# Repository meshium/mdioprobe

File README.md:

# mdioprobe v2

An MDIO probe on a custom STM32G474CET6 board: it watches a Clause-22 bus
without touching it, and it can drive one.

- **Passive capture.** The analogue MDIO and MDC lines go through comparators
  with a DAC threshold; TIM3 counts 32 MDC edges from the start bit, an HRTIM
  latch turns that into chip-select for SPI2 in slave mode, and the CPU only
  decodes finished frames. No per-frame software setup, so a busy bus does
  not outrun it — 284350 consecutive frames from an 88E6321 PPU at 6.25 MHz
  MDC with no decode errors, ring overruns or DMA faults.
- **Active master.** Bit-banged Clause 22 up to 2.5 MHz through a tri-state
  buffer powered from a programmable supply, so MDC comes out at the target's
  own logic level. Reads go back through the same comparator front end, which
  is why no receive-side translator is needed.
- **Level-agnostic.** The target's rail is measured, not assumed: 1.8, 2.5 and
  3.3 V buses are detected and every threshold derives from that one number.
  Until a rail is known, capture and the master both refuse to run.
- **Chip identification.** Registers 2 and 3 are looked up in a table
  extracted from the Linux kernel sources — 302 PHYs and 120 DSA switches,
  frozen into the firmware, so it works on a blank volume.

The command interface is a MicroPython CLI over USB CDC ACM, with history,
TAB completion, output redirection to files and a QSPI NOR volume for scripts
and logs.

```
mdio /flash> probe
phy 05: 4f51e91a  YT8531S Gigabit Ethernet
1 device(s) answered with an identifier

mdio /flash> read 5 2-3
reg 0x02 = 0x4f51
reg 0x03 = 0xe91a
```

## Building

Zephyr, with the board definition in-tree. The MicroPython submodule is
needed first:

```
git submodule update --init --recursive
./build.sh              # build
./build.sh flash        # build and flash over SWD
```

`build.sh` is the only supported entry point. It sources the Zephyr
environment, pins a toolchain and calls `west`, and it takes nothing on trust
from the machine it runs on:

| | |
| :-- | :-- |
| `ZEPHYR_BASE` | the Zephyr tree; defaults to `~/zephyrproject/zephyr` |
| `MDIOPROBE_SDK` | which SDK; defaults to the newest `~/zephyr-sdk-*` |
| `MDIOPROBE_VENV` | virtualenv to activate, and only when `west` is not already on `PATH` |

If your Zephyr environment is already active, the script uses it and changes
nothing. If a path is missing it says which one, rather than failing deep
inside CMake.

## Console

There is no VCP on the board. The log and the CLI share **USB CDC ACM**
(`/dev/tty.usbmodem*`); SWD on PA13/PA14/PB3 is for debugging. `tools/con.py`
is the bench driver for the console.

`help` lists the commands and `help <command>` explains one. USB is either the
console or a mass-storage device, never both at once: `msd` hands the volume
to the host and takes the console away until the probe is unplugged.

## Layout

```
src/            firmware; the public surface is include/mdioprobe_api.h alone
src/python/     the CLI, frozen into the image
boards/         the board definition (HWMv2)
hardware/       KiCad project: schematic, PCB, gerbers
docs/CAPTURE.md   how a frame is captured, end to end
docs/HARDWARE.md  pinout, connector, and what the schematic actually does
tools/con.py    console driver for the bench
tools/upload.py put files on the volume without unplugging
```

Zephyr APIs are used for ADC, GPIO, flash, UART, I2C and USB; the comparators,
TIM3, HRTIM, the SPI2 slave ring and the bit-bang master are driven through
STM32Cube LL and direct register writes, because Zephyr does not expose the
COMP-to-timer crossbars and its STM32 SPI slave driver races its own DMA.

## Status

Pre-release. Bring-up is complete and verified on hardware, including capture
against a real external master. Not yet exercised: the `uart` and `i2c`
connector personalities, and the short-circuit latch on the programmable
supply.

## Licence

Two objects, licensed separately, which is the usual practice for open
hardware and the only one that reads sensibly — a software licence does not
define what "object form" or "linking" mean for a printed circuit board.

- **Firmware and everything else: Apache-2.0**, text in `LICENSE`. The image
  is a static link, so a binary release carries Zephyr, MicroPython, the
  STM32Cube LL drivers, FatFs and picolibc with it; `NOTICE` lists each
  component and its terms and belongs with the binary, not only with the
  source.
- **The board, under `hardware/`: CERN-OHL-P-2.0**, text in
  `hardware/LICENSE`. Permissive, to match the firmware, and written for
  hardware — unlike a Creative Commons licence it grants patent rights, which
  for a circuit board is the part that matters.

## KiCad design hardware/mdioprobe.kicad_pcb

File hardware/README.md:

# mdioprobe v2 — board

SPDX-License-Identifier: CERN-OHL-P-2.0

KiCad 8 project for the probe: schematic, PCB, the footprints that are not in
the standard libraries, and a gerber set.

```
mdioprobe.kicad_sch     schematic
mdioprobe.kicad_pcb     board
mdioprobe.netlist       netlist
footprints.pretty/      footprints not in the KiCad libraries
gbr/                    gerbers and drill files
```

The KiCad footprint cache (`fp-info-cache`) and per-user project settings
(`*.kicad_prl`) are not tracked: KiCad rebuilds the first from the libraries
on demand, and the second is local to whoever opened the project.

## Licence

Everything in this directory is under the **CERN Open Hardware Licence
Version 2 — Permissive** (`LICENSE` here, SPDX `CERN-OHL-P-2.0`).

**The firmware is not.** The rest of the repository is Apache-2.0, with its
own `LICENSE` and `NOTICE` at the top level. Hardware and software are
different objects in law and are licensed separately, which is the usual
practice and the only one that makes sense: a software licence has nothing to
say about what "object form" or "linking" mean for a printed circuit board.

CERN-OHL-P rather than a Creative Commons licence, for two reasons. It is
written for hardware — it defines Source as the design files, Product as the
thing you build from them, and it covers making and having made, none of
which a licence written for creative works addresses. And it grants patent
rights (§6.1), which CC 4.0 explicitly does not (§2(b)(2): "Patent and
trademark rights are not licensed"). For hardware that gap is in exactly the
place the risk lives — the design files would be yours to copy while the
right to build the thing was not.

Permissive rather than the reciprocal variant (CERN-OHL-S): it matches the
firmware's Apache-2.0, and the point of publishing this board is that people
can use it, including inside something they do not open.

There is no warranty and no liability, per sections 5 and 8 of the licence.
This is a bench instrument, not a certified one.

## What it is

STM32G474CET6 in LQFP48. Comparators with a DAC threshold on the MDIO and MDC
inputs, a tri-state buffer on the MDC output powered from a programmable
soft-LDO so the probe drives at the target's own logic level, QSPI NOR for
storage, and USB.

`docs/HARDWARE.md` in the repository root is the pinout, the connector, and
the parts of the schematic worth knowing about before changing anything —
including what the next board revision needs.

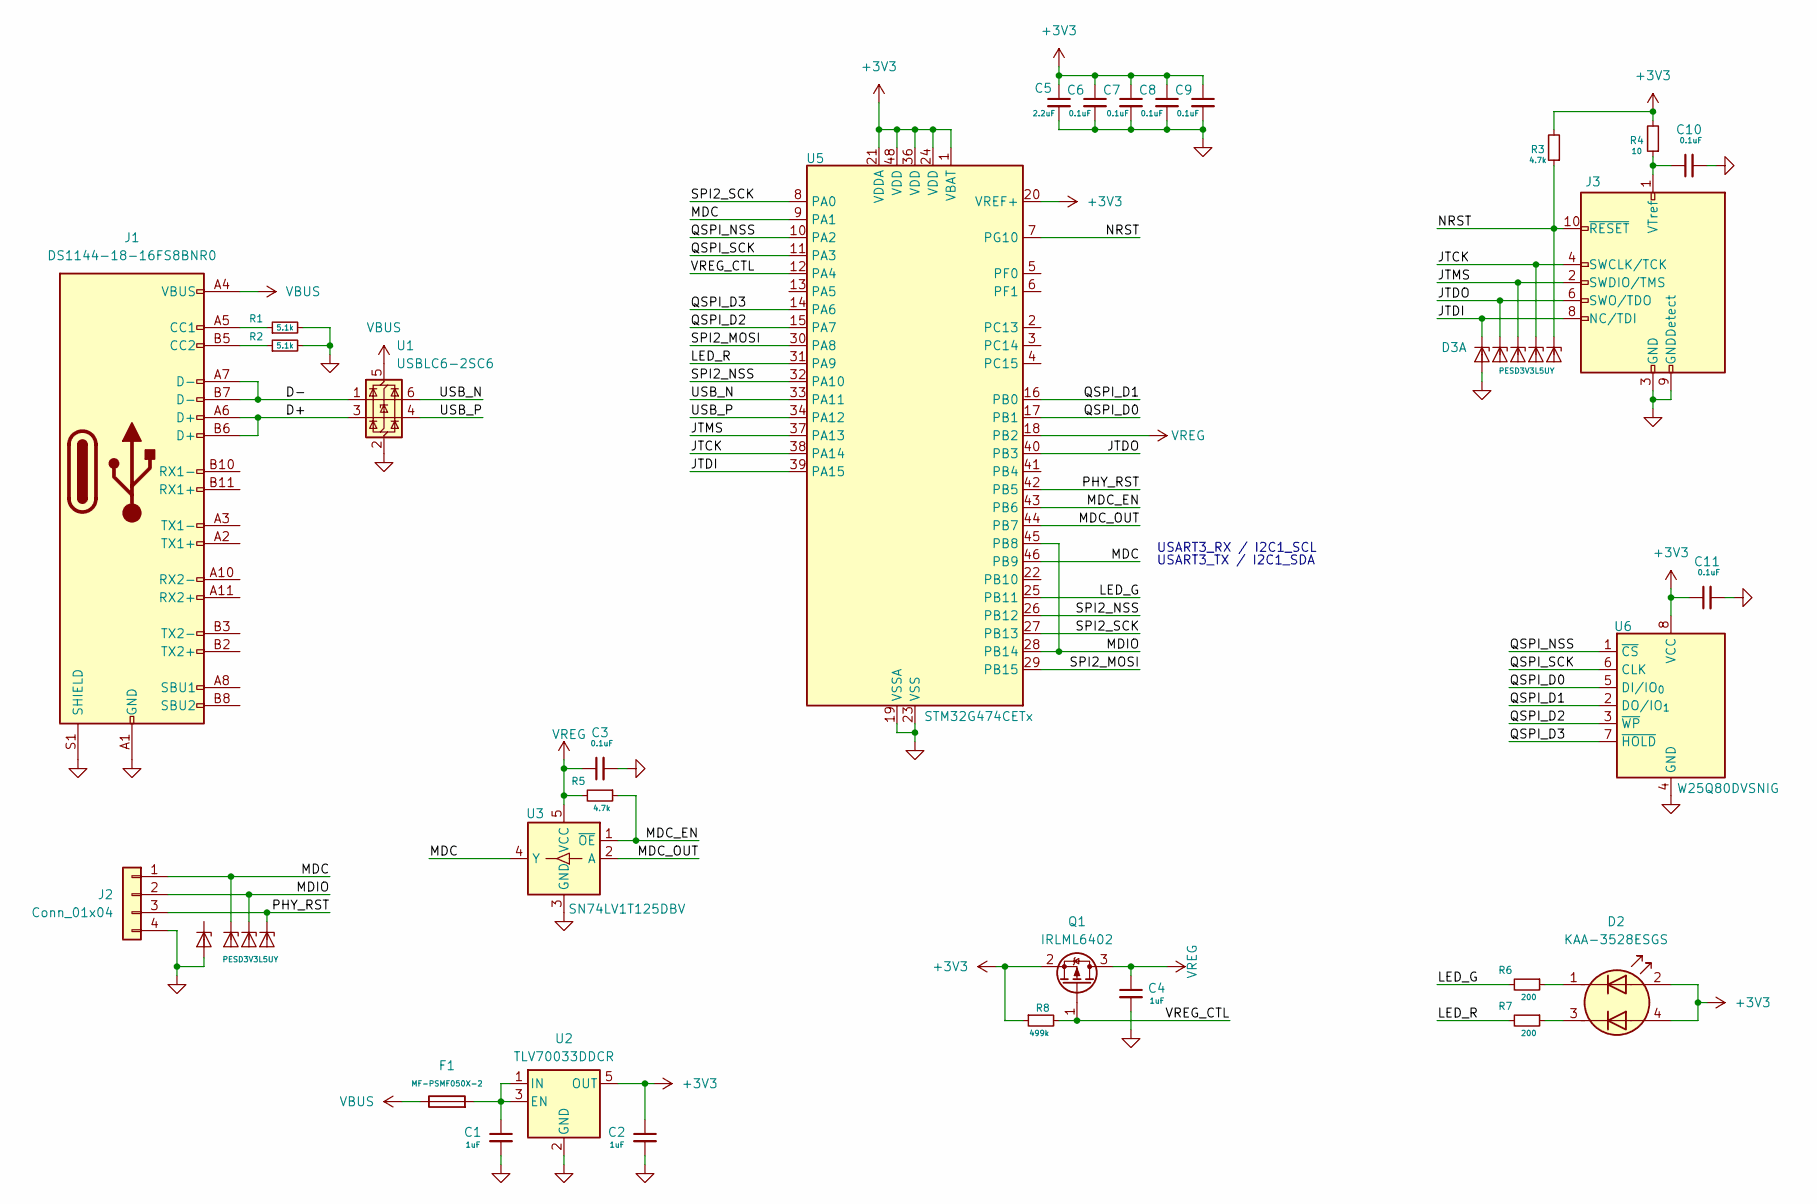
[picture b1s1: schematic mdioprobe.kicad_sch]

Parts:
C1, C2, C4: 1uF; C_0402_1005Metric
C3, C6, C7, C8, C9, C10, C11: 0.1uF; C_0402_1005Metric
C5: 2.2uF; C_0402_1005Metric
D1, D3: PESD3V3L5UY; SOT-363_SC-70-6
D2: KAA-3528ESGS; LED_Kingbright_AAA3528ESGCT
F1: MF-PSMF050X-2; Fuse_0805_2012Metric
J1: DS1144-18-16FS8BNR0; USB_C_Receptacle_DS1144-18
J2: Conn_01x04; PinHeader_1x04_P2.54mm_Horizontal
J3: Conn_ARM_JTAG_SWD_10; PinHeader_2x05_P1.27mm_Vertical
Q1: IRLML6402; SOT-23
R1, R2: 5.1k; R_0402_1005Metric
R3, R5: 4.7k; R_0402_1005Metric
R4: 10; R_0402_1005Metric
R6, R7: 200; R_0402_1005Metric
R8: 499k; R_0402_1005Metric
U1: USBLC6-2SC6; SOT-23-6L
U2: TLV70033DDCR; TSOT-23-5
U3: SN74LV1T125DBV; SOT-23-5
U5: STM32G474CETx; LQFP-48_7x7mm_P0.5mm
U6: W25Q80DVSNIG; SOIC-8_3.9x4.9mm_P1.27mm

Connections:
+3V3: C2.1, C5.1, C6.1, C7.1, C8.1, C9.1, C11.1, D2.2 (A1), D2.4 (A2), Q1.2 (S), R3.2, R4.2, R8.1, U2.5 (OUT), U5.1 (VBAT), U5.20 (VREF+), U5.21 (VDDA), U5.24 (VDD), U5.36 (VDD), U5.48 (VDD), U6.8 (VCC)
/D+: J1.A6 (D+), J1.B6 (D+), U1.3 (I/O2)
/D-: J1.A7 (D-), J1.B7 (D-), U1.1 (I/O1)
/JTCK: D3.5 (K4), J3.4 (SWCLK/TCK), U5.38 (PA14)
/JTDI: D3.1 (K1), J3.8 (NC/TDI), U5.39 (PA15)
/JTDO: D3.3 (K2), J3.6 (SWO/TDO), U5.40 (PB3)
/JTMS: D3.4 (K3), J3.2 (SWDIO/TMS), U5.37 (PA13)
/LED_G: R6.2, U5.25 (PB11)
/LED_R: R7.2, U5.31 (PA9)
/MDC: D1.6, J2.1, U3.4 (Y), U5.9 (PA1), U5.46 (PB9)
/MDC_EN: R5.1, U3.1 (~OE), U5.43 (PB6)
/MDC_OUT: U3.2 (A), U5.44 (PB7)
/MDIO: D1.5, J2.2, U5.28 (PB14), U5.45 (PB8)
/NRST: D3.6 (K5), J3.10 (~RESET), R3.1, U5.7 (PG10)
/PHY_RST: D1.4, J2.3, U5.42 (PB5)
/QSPI_D0: U5.17 (PB1), U6.5 (DI/IO_{0})
/QSPI_D1: U5.16 (PB0), U6.2 (DO/IO_{1})
/QSPI_D2: U5.15 (PA7), U6.3 (~WP)
/QSPI_D3: U5.14 (PA6), U6.7 (~HOLD)
/QSPI_NSS: U5.10 (PA2), U6.1 (~CS)
/QSPI_SCK: U5.11 (PA3), U6.6 (CLK)
/SPI2_MOSI: U5.29 (PB15), U5.30 (PA8)
/SPI2_NSS: U5.26 (PB12), U5.32 (PA10)
/SPI2_SCK: U5.8 (PA0), U5.27 (PB13)
/USB_N: U1.6 (I/O1), U5.33 (PA11)
/USB_P: U1.4 (I/O2), U5.34 (PA12)
/VREG_CTL: Q1.1 (G), R8.2, U5.12 (PA4)
GND: C1.2, C2.2, C3.2, C4.2, C5.2, C6.2, C7.2, C8.2, C9.2, C10.2, C11.2, D1.2, D3.2 (A), J1.A1 (GND), J1.A12 (GND), J1.B1 (GND), J1.B12 (GND), J1.S1 (SHIELD), J2.4, J3.3 (GND), J3.5 (GND), J3.9 (GNDDetect), R1.2, R2.2, U1.2 (GND), U2.2 (GND), U3.3 (GND), U5.19 (VSSA), U5.23 (VSS), U5.35 (VSS), U5.47 (VSS), U6.4 (GND)
unnamed: D2.1 (K1), R6.1
unnamed: D2.3 (K2), R7.1
unnamed: J1.A5 (CC1), R1.1
unnamed: J1.B5 (CC2), R2.1
unnamed: C10.1, J3.1 (VTref), R4.1
unnamed: C1.1, F1.2, U2.1 (IN), U2.3 (EN)
VBUS: F1.1, J1.A4 (VBUS), J1.A9 (VBUS), J1.B4 (VBUS), J1.B9 (VBUS), U1.5 (VBUS)
VREG: C3.1, C4.1, Q1.3 (D), R5.2, U3.5 (VCC), U5.18 (PB2)

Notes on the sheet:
USART3_RX / I2C1_SCL
USART3_TX / I2C1_SDA

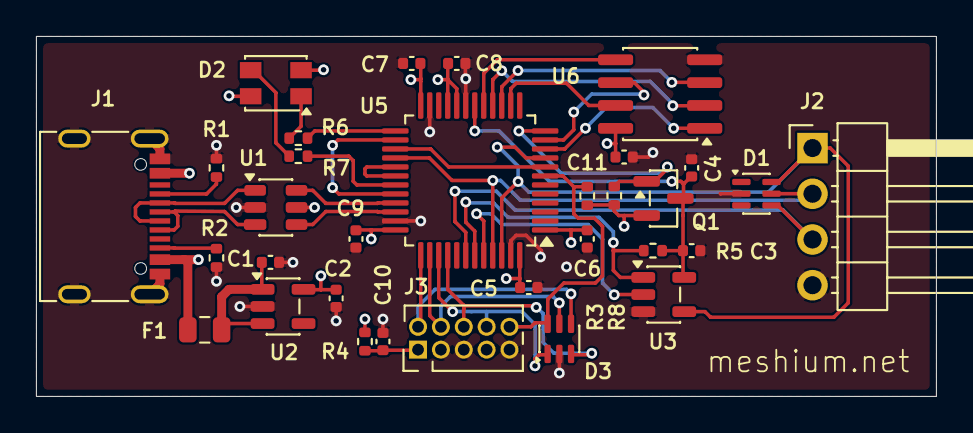
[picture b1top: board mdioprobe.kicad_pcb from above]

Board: 4 copper layers, 50.0 x 20.0 mm, 32 parts (0 on the bottom side), 36 nets.

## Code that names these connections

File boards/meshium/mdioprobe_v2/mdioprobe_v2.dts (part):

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 * Capture path pin assignment is identical to the mdioprobe_g474 bring-up
 * board; what were jumper wires there are PCB traces here:
 *
 *   PA0 (COMP1_OUT, MDC digital)  --trace--> PB13 (SPI2_SCK)
 *   PA8 (COMP7_OUT, MDIO digital) --trace--> PB15 (SPI2_MOSI)
 *   PA10 (HRTIM1_CHB1, NSS latch) --trace--> PB12 (SPI2_NSS)
 *
 * Everything on the capture chain (COMP1/COMP7, DAC3/DAC4 thresholds,
 * TIM3 one-pulse counter, HRTIM SR-latch, SPI2 slave + DMA1) is set up
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
	/*
	 * Colours verified on hardware 2026-07-22: the initial pinout notes
	 * had them the other way round (PA9=R, PB11=G) — the board actually
	 * wires PA9 to green and PB11 to red.
	 */
	leds: leds {
		compatible = "gpio-leds";

		green_led: led_g {
			gpios = <&gpioa 9 GPIO_ACTIVE_LOW>;
			label = "LED_G";
		};

		red_led: led_r {
			gpios = <&gpiob 11 GPIO_ACTIVE_LOW>;
			label = "LED_R";
		};
	};

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	 * Bitbang Clause-22 master (the "generate" half of the probe).
	 *
	 * MDC leaves the board through an external tri-state buffer:
	 *   MDC_EN  (PB6, active LOW) enables the buffer output;
	 *   MDC_OUT (PB7) is the bitbang clock fed into the buffer input.
	 * The buffer is powered from the programmable translator supply
	 * (see mdioprobe_vreg.c) so MDC swings at the target's logic level.
	 * Its output also loops back to PA1/COMP1, so the sniffer's clock
	 * front end sees the probe's own MDC.
	 *
	 * MDIO is split: PB8 drives the line (open-drain, no pull, parked
	 * as Analog while receiving so it cannot load the bus), while the
	 * read-back path is the *sniffer* front end — PB14 → COMP7, whose
	 * digital output the master samples. Reading through the comparator
	 * means the master works at whatever logic level the target uses,
	 * with the same DAC threshold the capture path was calibrated to.
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	mdio_master: mdio_master {
		compatible = "mdioprobe,mdio-master";
		status = "okay";
		mdc-gpios = <&gpiob 7 GPIO_ACTIVE_HIGH>;
		/*
		 * Open-drain: a 4.7 kΩ pull-up to VREG (the buffer's supply)
		 * makes the inactive level. Driving it push-pull would
		 * back-power the VREG rail from the 3.3 V domain.
		 */
		mdc-en-gpios = <&gpiob 6 (GPIO_ACTIVE_LOW | GPIO_OPEN_DRAIN)>;
		mdio-out-gpios = <&gpiob 8 (GPIO_ACTIVE_HIGH | GPIO_OPEN_DRAIN)>;
	};

	mdioprobe_config {
		compatible = "mdioprobe,config";
		/*
		 * MDIO idle-voltage sense. PB14 is shared three ways:
		 * ADC1_IN5 (this channel), COMP7_INP (sniffer) and the
		 * bitbang master's read-back. All three are read-only —
		 * the pin stays Analog at all times.
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
/*
 * Drop the default internal pull-down from SPI2 SCK/MOSI. The bus is
 * push-pull driven on-die by COMP1_OUT (PA0) and COMP7_OUT (PA8) through
 * short PCB traces; a ~40 kΩ pull-down would skew rising edges at
 * multi-MHz MDC. NSS keeps its pull-up — the HRTIM latch (POL1=1) rests
 * it inactive HIGH between frames.
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
/*
 * SPI2 slave = the capture engine. The Zephyr driver is enabled only so
 * its init applies this pinctrl group (PB12/PB13/PB15 → AF5); the API is
 * never called. src/mdioprobe_mdio_api.c programs SPI2 + DMA1_Channel1 +
 * DMAMUX1 directly. Note PB14 is deliberately NOT listed — on this board
 * it is the analog MDIO sense pin, not SPI2_MISO.
 */
&spi2 {
	pinctrl-0 = <&spi2_sck_pb13_nopull &spi2_mosi_pb15_nopull &spi2_nss_pb12>;
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	#address-cells = <1>;
	#size-cells = <0>;

	/* PB14 = ADC1_IN5 — MDIO idle level (also COMP7_INP@INPSEL=0). */
	channel@5 {
		reg = <5>;
		zephyr,gain = "ADC_GAIN_1";
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};

/*
 * ADC2_IN12 (PB2, translator Vout sense) and DAC1_CH1 (PA4, MOSFET gate)
 * are driven from LL inside src/mdioprobe_vreg.c — the 10 kHz control
 * loop needs direct register access, so no Zephyr ADC/DAC node here.
 * DAC3_CH1 / DAC4_CH1 (comparator thresholds) are internal-only on G4:
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
/*
 * QSPI NOR: Winbond W25Q80DVSNIG, 8 Mbit, on bank 1.
 *   PA3 CLK, PA2 NCS, PB1 IO0, PB0 IO1, PA7 IO2, PA6 IO3.
 */
/ {
	/*
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/*
 * Alternate serial personalities of the target connector:
 *
 *   PB9 = USART3_TX / I2C1_SDA
 *   PB8 = USART3_RX / I2C1_SCL
 *
 * Both pins go straight to the connector, bypassing the MDC buffer — so
 * the serial personalities are fixed 3.3 V with no level translation, and
 * I2C1_SDA stays bidirectional end to end. The buffer must be off in these
 * modes or it would fight PB9 on the shared connector line.
 *
 * Both nodes are enabled so their drivers exist, but mdioprobe_serial.c
 * parks them in the "sleep" (Analog) pinctrl state at boot and only applies
 * "default" to the personality that is actually selected. In MDIO mode
 * neither peripheral may touch PB8/PB9 — anything driving those pins loads
 * the bus the analog front end is measuring.
 */
&usart3 {
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
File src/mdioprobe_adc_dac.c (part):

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{
	/*
	 * STM32G474CET6 pin map (post COMP7 / TIM3-OPM migration):
	 * - COMP1_INP: PA1  (MDC)           [INPSEL=0]
	 * - COMP7_INP: PB14 (MDIO)          [INPSEL=0]
	 * - COMP1_OUT: PA0  (AF8) → PCB trace to SPI2_SCK  (PB13)
	 * - COMP7_OUT: PA8  (AF8) → PCB trace to SPI2_MOSI (PB15)
	 *
	 * COMP outputs are also routed INTERNALLY to the frame-gating logic:
	 *   comp1_out → TIM3_ETR  (ETRSEL=0001)
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	 * - COMP1_INM: DAC3_CH1 (INMSEL=100)
	 * - COMP7_INM: DAC4_CH1 (INMSEL=100)
	 *
	 * Reserved pins (USB/JTAG/QSPI) kept free: PA2 PA3 PA6 PA7 PA11
	 * PA12 PA13 PA14 PA15 PB0 PB1 PB3.
	 */

	LL_AHB2_GRP1_EnableClock(LL_AHB2_GRP1_PERIPH_GPIOA);
	LL_AHB2_GRP1_EnableClock(LL_AHB2_GRP1_PERIPH_GPIOB);
	LL_APB2_GRP1_EnableClock(LL_APB2_GRP1_PERIPH_SYSCFG);

	/* PA1 (COMP1_INP) → Analog */
	LL_GPIO_SetPinMode(GPIOA, LL_GPIO_PIN_1, LL_GPIO_MODE_ANALOG);
	LL_GPIO_SetPinPull(GPIOA, LL_GPIO_PIN_1, LL_GPIO_PULL_NO);

	/* PB14 (COMP7_INP) → Analog (also ADC1_IN5) */
	LL_GPIO_SetPinMode(GPIOB, LL_GPIO_PIN_14, LL_GPIO_MODE_ANALOG);
	LL_GPIO_SetPinPull(GPIOB, LL_GPIO_PIN_14, LL_GPIO_PULL_NO);

	/* PA0 (COMP1_OUT) → AF8 */
	LL_GPIO_SetPinMode(GPIOA, LL_GPIO_PIN_0, LL_GPIO_MODE_ALTERNATE);
	LL_GPIO_SetAFPin_0_7(GPIOA, LL_GPIO_PIN_0, LL_GPIO_AF_8);
	LL_GPIO_SetPinSpeed(GPIOA, LL_GPIO_PIN_0, LL_GPIO_SPEED_FREQ_VERY_HIGH);

	/* PA8 (COMP7_OUT) → AF8 */
	LL_GPIO_SetPinMode(GPIOA, LL_GPIO_PIN_8, LL_GPIO_MODE_ALTERNATE);
	LL_GPIO_SetAFPin_8_15(GPIOA, LL_GPIO_PIN_8, LL_GPIO_AF_8);
	LL_GPIO_SetPinSpeed(GPIOA, LL_GPIO_PIN_8, LL_GPIO_SPEED_FREQ_VERY_HIGH);

	/* COMP1 (MDC) */
	LL_COMP_SetInputPlus(COMP1, LL_COMP_INPUT_PLUS_IO1); /* PA1 */
	LL_COMP_SetInputMinus(COMP1, LL_COMP_INPUT_MINUS_DAC3_CH1);
	LL_COMP_SetInputHysteresis(COMP1, LL_COMP_HYSTERESIS_NONE);
	LL_COMP_SetOutputPolarity(COMP1, LL_COMP_OUTPUTPOL_NONINVERTED);
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	LL_COMP_Enable(COMP1);

	/* COMP7 (MDIO) */
	LL_COMP_SetInputPlus(COMP7, LL_COMP_INPUT_PLUS_IO1); /* PB14 */
	LL_COMP_SetInputMinus(COMP7, LL_COMP_INPUT_MINUS_DAC4_CH1);
	LL_COMP_SetInputHysteresis(COMP7, LL_COMP_HYSTERESIS_NONE);
	LL_COMP_SetOutputPolarity(COMP7, LL_COMP_OUTPUTPOL_NONINVERTED);
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	 * MCR.MODE=011 "buffer disabled, internal only" mode keeps the
	 * unbuffered DAC node purely on-die, with no pad acting as an
	 * antenna or parasitic capacitance source. Compare DAC1/DAC2 which
	 * have external pins (PA4/PA5/...) and would capacitively couple
	 * switching noise from neighbouring AF outputs into the COMP_INM
	 * reference.
	 *
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
	/*
	 * Thresholds: DAC3_CH1 → COMP1_INM (MDC), DAC4_CH1 → COMP7_INM
	 * (MDIO). Both internal-only DACs on G474 — no pin coupling.
	 */
	mdioprobe_dac_thresholds_init();
	return 0;
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

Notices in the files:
boards/meshium/mdioprobe_v2/mdioprobe_v2.dts:
Copyright (c) 2026 Meshium
SPDX-License-Identifier: Apache-2.0
